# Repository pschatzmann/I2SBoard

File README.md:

# I2SBoard

An add-on board for the [GuitarPreAmp](https://github.com/pschatzmann/GuitarPreAmp) or the [PiezoPreAmp](https://github.com/pschatzmann/PiezoPreAmp). It turns the preamp output into
**I2S** for an **ESP32** or **RP2040**, using a PCM1808 stereo ADC. The microcontroller provides the master clock (MCLK, BCK, WS).
A **USB-C** connector powers this board and the preamp.

## Features

- PCM1808, 24-bit, up to 96 kHz, slave mode (MCLK, BCK and WS from the microcontroller), I2S format
- The preamp signal goes to **both** channels (left and right carry the same signal), so either I2S slot can be used
- USB-C (power only) with 5.1k CC resistors, PTC fuse and ESD diode; the 5 V also powers the preamp
- Optional `5V IN` header for an external 5 V module (for example a LiPo charger/boost module)
- On-board 3.3 V LDO for the ADC's digital supply, and a ferrite-filtered 5 V for its analog supply
- **47 x 29 mm, the same outline and the same four mounting holes as the preamp boards**; the headers line up with the preamp's J2 and J3
- Signal from the preamp **AUX** output: wide bandwidth (about 9 Hz to 126 kHz)

## Connecting the preamp

The board takes the **AUX output** of the preamp (0 V centred, wide bandwidth, no 13 kHz filter) and powers the preamp. The two headers sit at the
same positions as the matching headers of the preamp boards, so the boards stack directly (M2.5 standoffs, same orientation):

| This board | Position (pin 1) | Preamp header | Signal |
|---|---|---|---|
| J1, 2 pins vertical | (41.5, 8.5) mm | pins 1-2 of J2 | `5V` (to the preamp), `GND` |
| J2, 2 pins horizontal | (28.0, 27.0) mm | J3 (AUX OUT) | `AUX` (from the preamp), `GND` |

Pins 3-4 of the preamp's J2 (OUT, GND) are not used. Use female sockets on J1 and J2 of this board (the preamp's J3 must be populated), or short
wires. The gain trimmer of the preamp is covered when stacked: set the gain before you stack the boards.

## Connecting the microcontroller (J3, bottom edge, 3.3 V logic)

| Pin | Signal | Direction |
|---|---|---|
| 1 | GND | |
| 2 | MCLK | microcontroller -> board |
| 3 | BCK | microcontroller -> board |
| 4 | WS (LRCK) | microcontroller -> board |
| 5 | DOUT | board -> microcontroller |
| 6 | GND | |

Connect the GND of the microcontroller. There is no power pin on this header: the board takes its power from USB-C (or J5).
Use fs = 48 kHz with MCLK = 12.288 MHz (256 fs) and BCK = 3.072 MHz (64 x fs), 24-bit I2S. The ADC auto-detects 256, 384 or 512 x fs.
The microcontroller must generate MCLK before it reads the data and keep it running. Wait about 2 s after power-up before using
samples: the coupling capacitors need about 1.7 s to settle.

### 16-bit or 24-bit data

The PCM1808 always outputs **24-bit I2S**, and it needs **64 BCK clocks per frame** (or 48 when MCLK is 384 x fs). A 32-BCK frame (16 bit slots)
is not supported. So each channel slot is 32 bits wide: the 24 data bits come first, MSB first, followed by padding. To get **16-bit** samples,
keep the clocks the same and read only the top 16 bits of each slot; no hardware change is needed.

- **ESP32:** set the data width to 16 bits and the slot width to 32 bits, so BCK stays at 64 x fs (3.072 MHz at 48 kHz). In ESP-IDF v5 that is
  `data_bit_width = 16` and `slot_bit_width = 32`. Alternatively read 32-bit words and shift them right by 16.
- **RP2040:** let the PIO program shift in 32 bits per channel and keep the upper 16 bits.

Reading 16 bits gives about 96 dB of dynamic range, slightly below the ADC's roughly 97 dB at 3 Vpp. For a guitar or piezo preamp that is usually
enough. Read the full 24 bits if you want to process the quiet end of the signal.

## Power

USB-C 5 V -> PTC (500 mA) -> 5 V rail -> preamp (J1 pin 1), 3.3 V LDO and the filtered analog 5 V. The LED shows that the rail is on.
`5V IN` (J5) feeds the same rail through a Schottky diode: use one source at a time. Never connect the 5 V of this board to a 3.3 V pin.

## Battery

There is no LiPo charger on this board on purpose (the boost converter would add switching noise next to the ADC, and the
design is not tested yet). Use a charger/boost module on `5V IN`.

## Simulation

The analog input and the power path were simulated with ngspice (`python3 tools/sim.py`, results in [sim/results.txt](sim/results.txt)).
Summary: -3 dB from 9.4 Hz to 126 kHz, 3.3 Vpp from the preamp becomes 2.70 Vpp at the ADC (no clipping from VCC 4.5 to 5.5 V), start-up
settling about 1.7 s, the ADC supply is 4.74 V or more even at the USB minimum of 4.75 V, hot-plug peak on the ADC supply 5.4 V (6.3 V in a
pessimistic model, limit 6.5 V). The PCM1808 itself, the I2S timing and the microcontroller are not simulated.

## Ordering from JLCPCB

Files are in [fab/](fab/): `I2SBoard_gerber.zip`, `BOM.csv`, `CPL.csv`.
1. Upload the Gerber zip, enable **PCB Assembly** (top side), add `BOM.csv` and `CPL.csv`.
2. In the 3D preview check the part rotations (PCM1808, SOT-23-5, USB-C, diodes).
3. Check stock and extended-part fees (the USB-C connector and the PCM1808 are probably extended parts).
4. Order the minimum quantity first, since the design is untested.
Headers (J1, J2, J3, J5) are not assembled; solder them yourself.

## Project files and regeneration

See [SPEC.md](SPEC.md) for the full specification and bill of materials. The KiCad files are generated from
[tools/design.py](tools/design.py):

```bash
cd tools
python3 gen_sch.py ../kicad/I2SBoard.kicad_sch   # schematic
./route.sh                                       # board, Freerouting, design-rule check
python3 export_jlc.py                            # fab/ files
python3 sim.py                                   # simulation
```

KiCad 9, Java and [Freerouting](https://github.com/freerouting/freerouting) at `~/tools/freerouting/freerouting.jar` are needed.
Freerouting is not deterministic, so run `route.sh` again if it leaves a connection open. After `route.sh`, check that
`kicad/I2SBoard.kicad_pro` has a default netclass clearance of 0.15 mm (the USB-C pads need it).

## Status

Untested design. The KiCad design-rule check (0 errors, 0 unconnected, silkscreen warnings only), the board outline, the mounting
holes and the J1 / J2 positions against the preamp boards, and the simulation above were checked. It has not been built or tested with an
ESP32 or RP2040.

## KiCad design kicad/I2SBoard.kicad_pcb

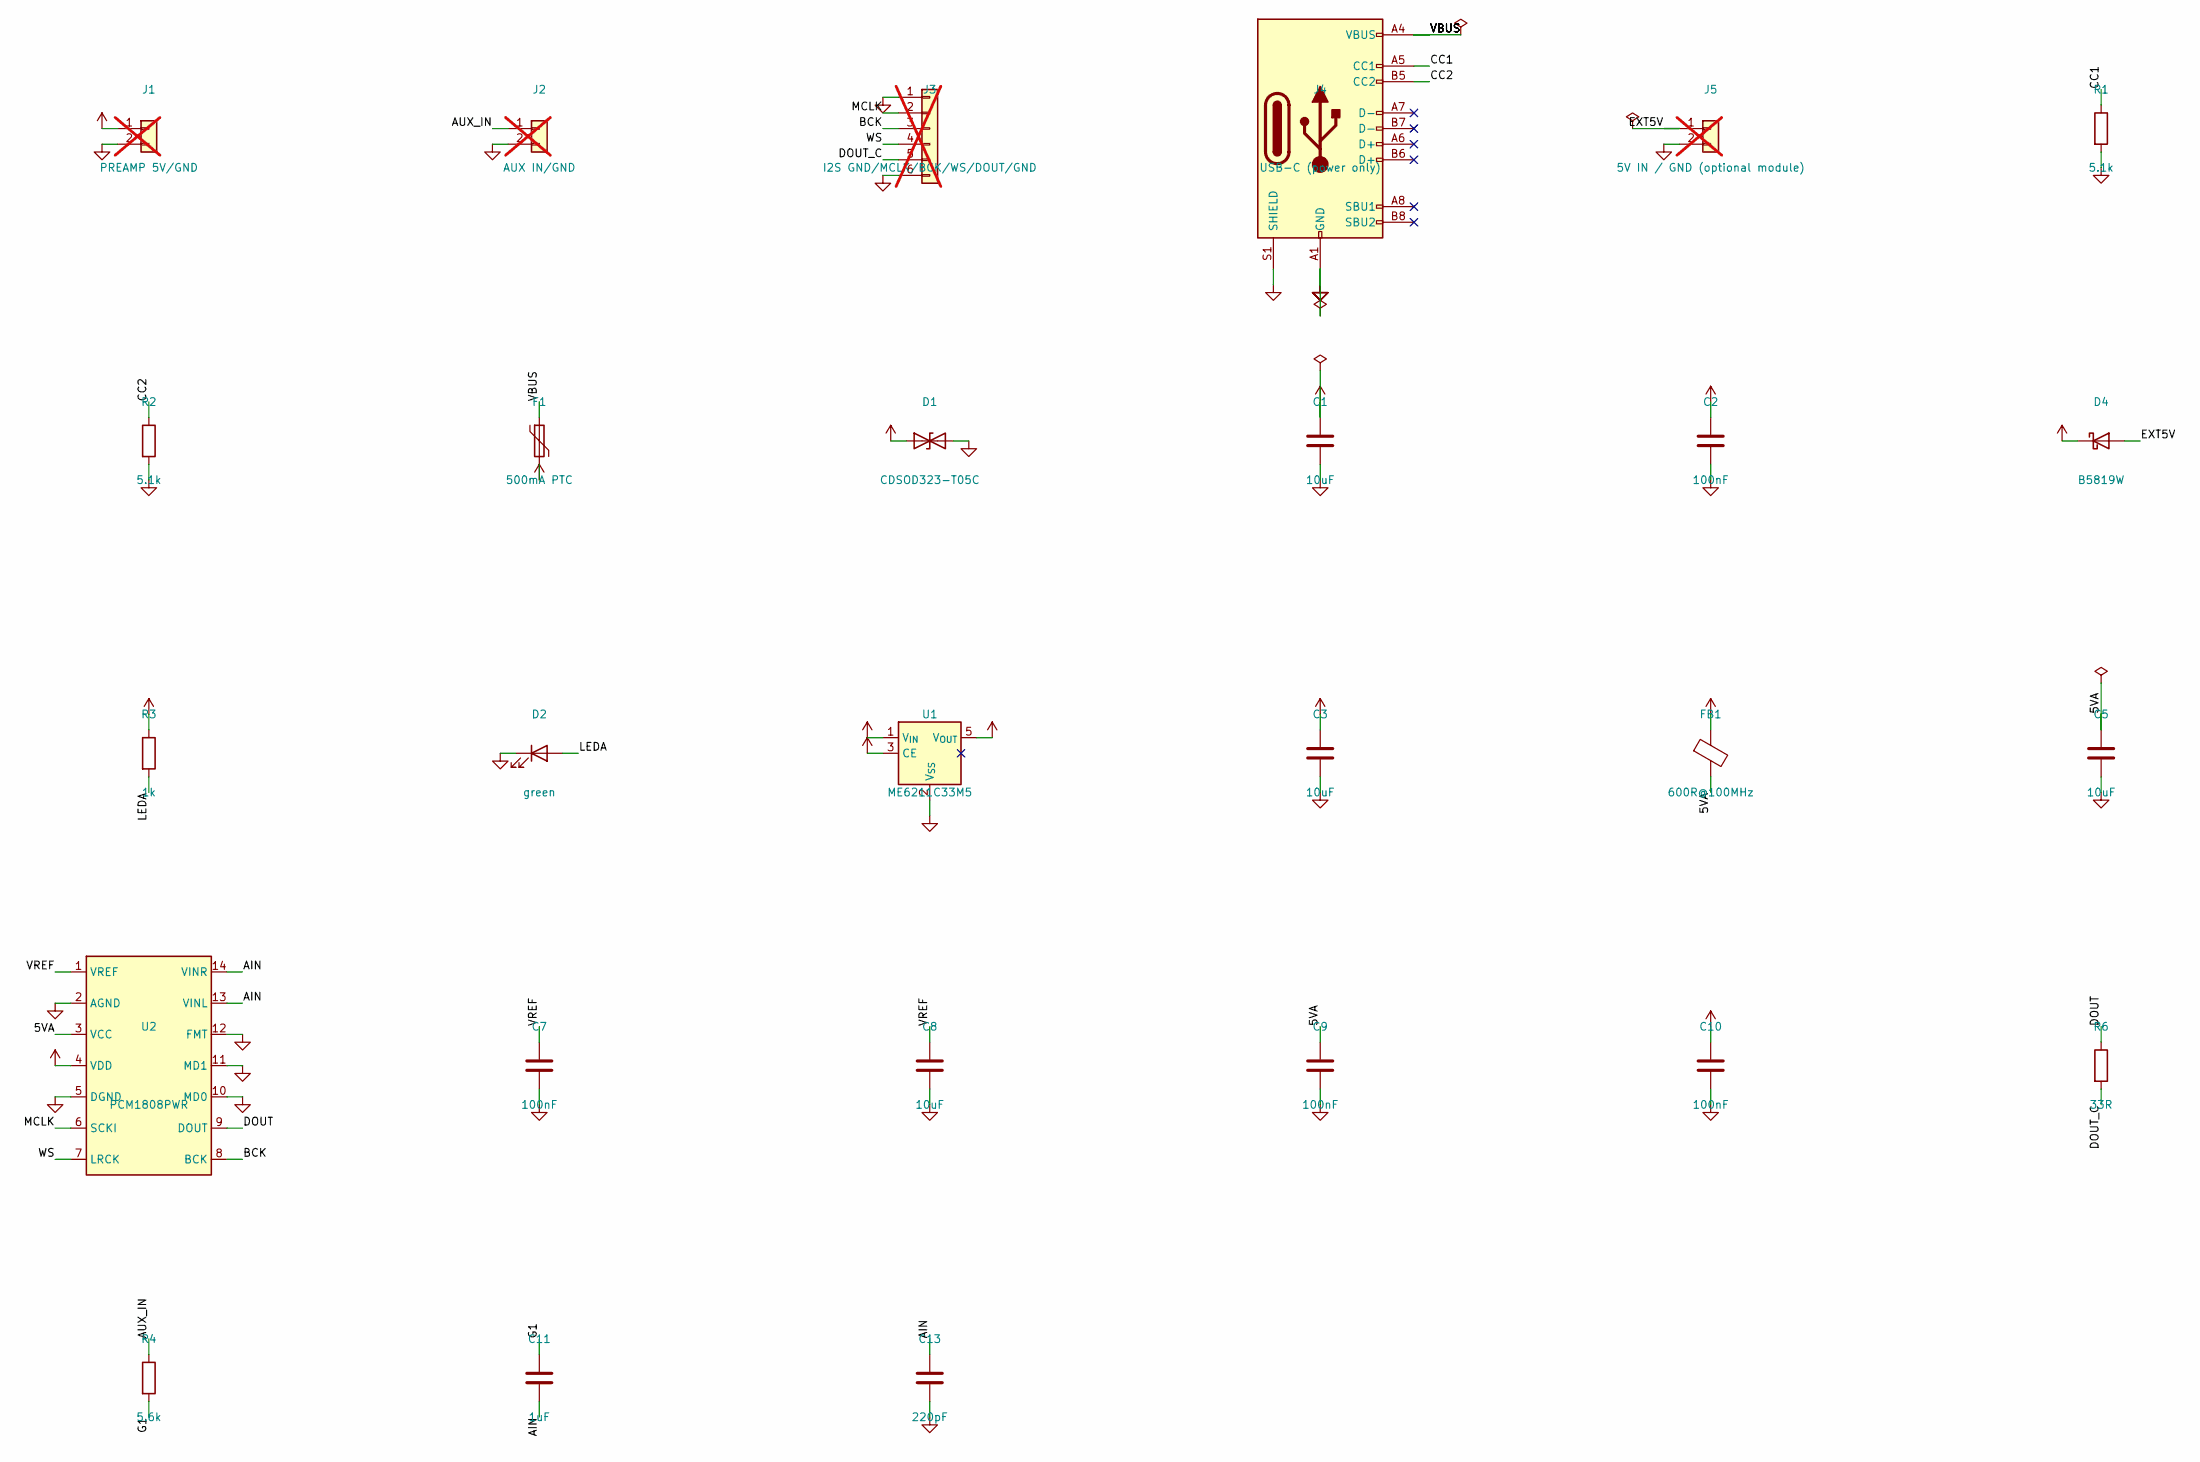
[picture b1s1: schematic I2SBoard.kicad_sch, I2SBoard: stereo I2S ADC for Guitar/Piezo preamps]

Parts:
C1, C3, C5, C8: 10uF; C_0805_2012Metric
C2, C7, C9, C10: 100nF; C_0603_1608Metric
C11: 1uF; C_0603_1608Metric
C13: 220pF; C_0603_1608Metric
D1: CDSOD323-T05C; D_SOD-323
D2: green; LED_0603_1608Metric
D4: B5819W; D_SOD-123
F1: 500mA PTC; Fuse_1206_3216Metric
FB1: 600R@100MHz; L_0603_1608Metric
J1: PREAMP 5V/GND; PinHeader_1x02_P2.54mm_Vertical; not fitted
J2: AUX IN/GND; PinHeader_1x02_P2.54mm_Vertical; not fitted
J3: I2S GND/MCLK/BCK/WS/DOUT/GND; PinHeader_1x06_P2.54mm_Vertical; not fitted
J4: USB-C (power only); USB_C_Receptacle_HRO_TYPE-C-31-M-12
J5: 5V IN / GND (optional module); PinHeader_1x02_P2.54mm_Vertical; not fitted
R1, R2: 5.1k; R_0603_1608Metric
R3: 1k; R_0603_1608Metric
R4: 5.6k; R_0603_1608Metric
R6: 33R; R_0603_1608Metric
U1: ME6211C33M5; SOT-23-5
U2: PCM1808PWR; TSSOP-14_4.4x5mm_P0.65mm

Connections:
5VA: C5.1, C9.1, FB1.2, U2.3 (VCC)
+3V3: C3.1, C10.1, U1.5 (V_{OUT}), U2.4 (VDD)
+5V: C1.1, C2.1, D1.1 (A1), D4.1 (K), F1.2, FB1.1, J1.1, R3.1, U1.1 (V_{IN}), U1.3 (CE)
AIN: C11.2, C13.1, U2.13 (VINL), U2.14 (VINR)
AUX_IN: J2.1, R4.1
BCK: J3.3, U2.8 (BCK)
CC1: J4.A5 (CC1), R1.1
CC2: J4.B5 (CC2), R2.1
DOUT: R6.1, U2.9 (DOUT)
DOUT_C: J3.5, R6.2
EXT5V: D4.2 (A), J5.1
G1: C11.1, R4.2
GND: C1.2, C2.2, C3.2, C5.2, C7.2, C8.2, C9.2, C10.2, C13.2, D1.2 (A2), D2.1 (K), J1.2, J2.2, J3.1, J3.6, J4.A1 (GND), J4.A12 (GND), J4.B1 (GND), J4.B12 (GND), J4.S1 (SHIELD), J5.2, R1.2, R2.2, U1.2 (V_{SS}), U2.2 (AGND), U2.5 (DGND), U2.10 (MD0), U2.11 (MD1), U2.12 (FMT)
LEDA: D2.2 (A), R3.2
MCLK: J3.2, U2.6 (SCKI)
VBUS: F1.1, J4.A4 (VBUS), J4.A9 (VBUS), J4.B4 (VBUS), J4.B9 (VBUS)
VREF: C7.1, C8.1, U2.1 (VREF)
WS: J3.4, U2.7 (LRCK)

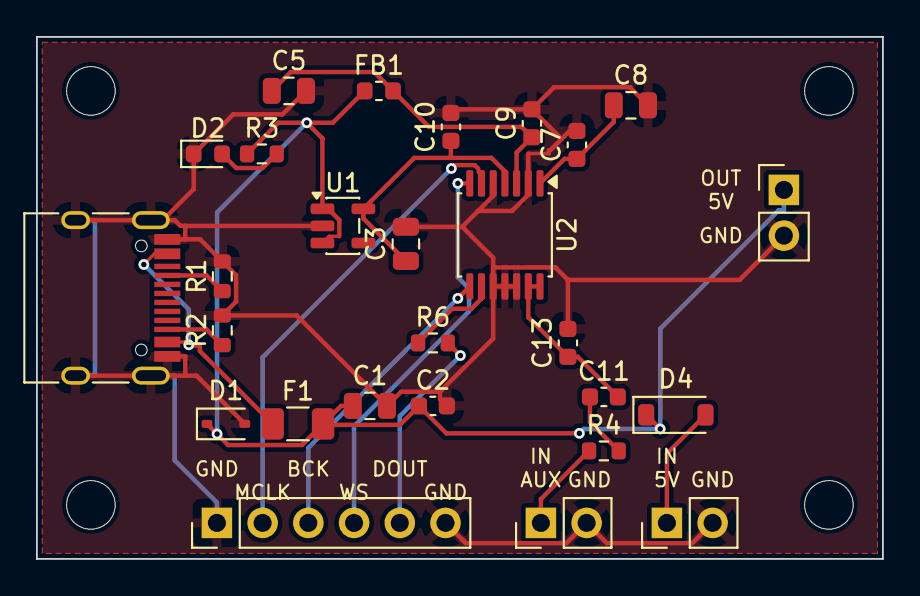
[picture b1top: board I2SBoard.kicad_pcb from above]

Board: 2 copper layers, 47.0 x 29.0 mm, 31 parts (0 on the bottom side), 18 nets.

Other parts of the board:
H1, H2, H3, H4: MountingHole_2.7mm_M2.5

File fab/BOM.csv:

Comment,Designator,Footprint,LCSC Part #
USB-C (power only),J4,USB_C_Receptacle_HRO_TYPE-C-31-M-12,C165948
5.1k,"R1,R2",R_0603_1608Metric,C23186
500mA PTC,F1,Fuse_1206_3216Metric,C163512
CDSOD323-T05C,D1,D_SOD-323,C711706
10uF,"C1,C3,C5,C8",C_0805_2012Metric,C15850
100nF,"C2,C7,C9,C10",C_0603_1608Metric,C1591
B5819W,D4,D_SOD-123,C64885
1k,R3,R_0603_1608Metric,C21190
green,D2,LED_0603_1608Metric,C2289
ME6211C33M5,U1,SOT-23-5,C82942
600R@100MHz,FB1,L_0603_1608Metric,C19330
PCM1808PWR,U2,TSSOP-14_4.4x5mm_P0.65mm,C55513
33R,R6,R_0603_1608Metric,C23140
5.6k,R4,R_0603_1608Metric,C23189
1uF,C11,C_0603_1608Metric,C15849
220pF,C13,C_0603_1608Metric,C156398
